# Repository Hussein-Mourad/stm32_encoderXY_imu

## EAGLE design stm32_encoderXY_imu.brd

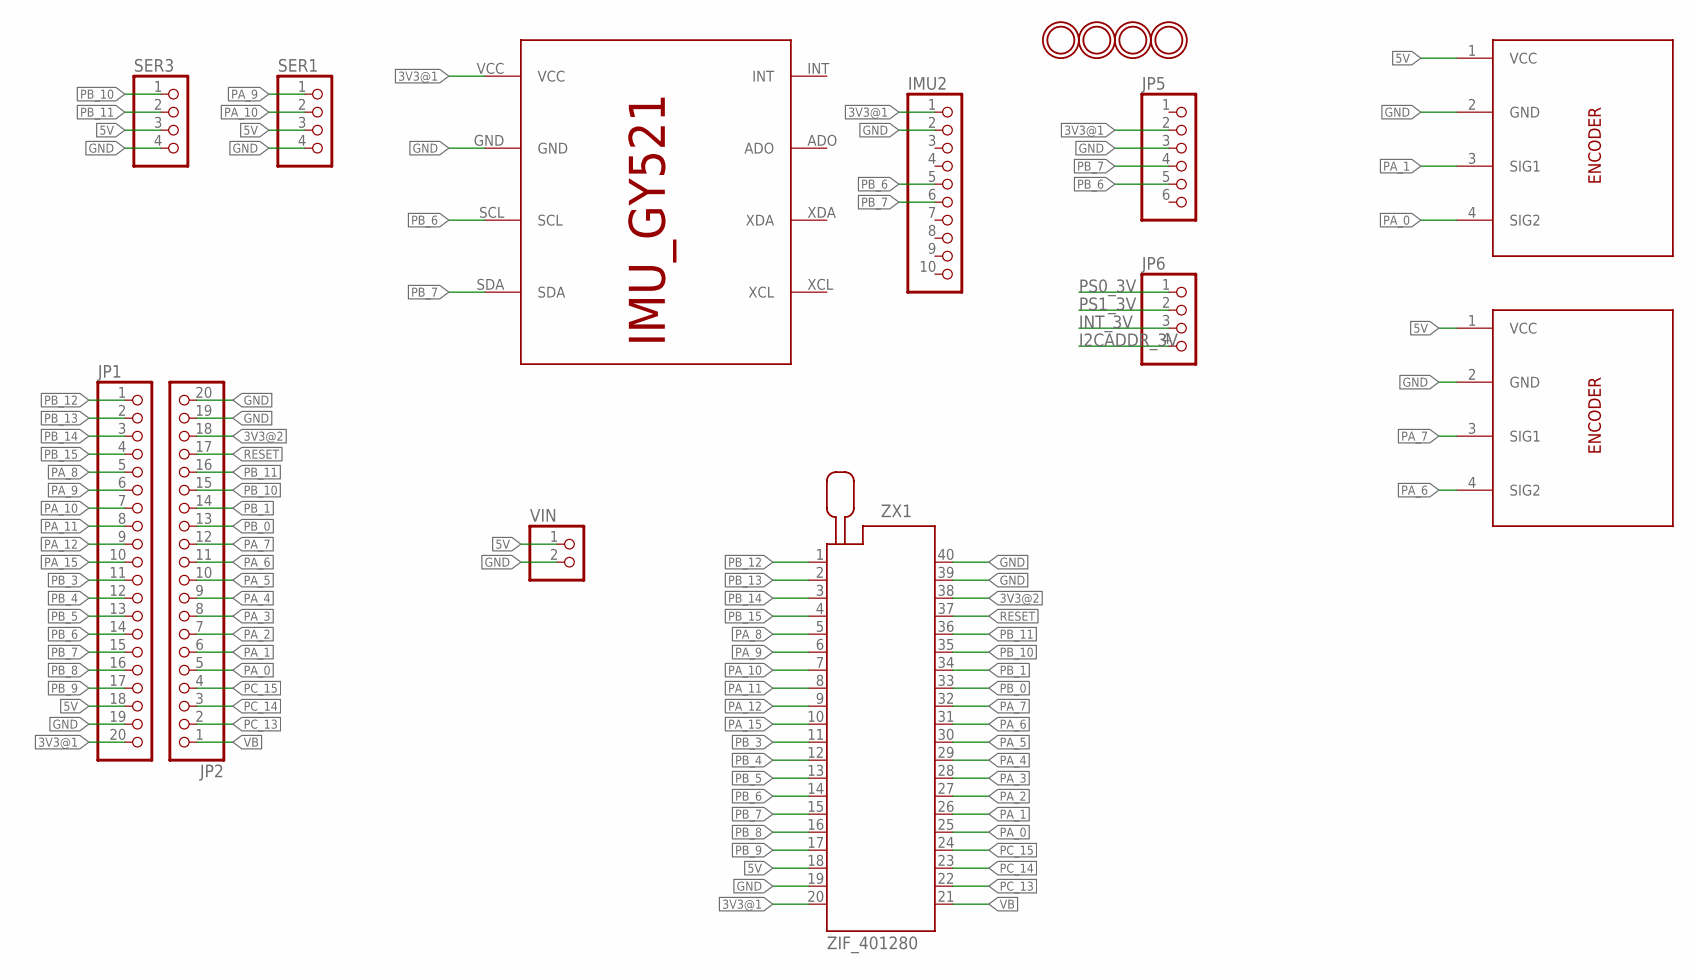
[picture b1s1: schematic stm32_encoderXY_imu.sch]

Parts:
ENC1: ENC_Y; 1X04_DATA
ENC2: ENC_X; 1X04_DATA
IMU1: IMU_ROBOCON_GY521; IMU_GY521
IMU2: PINHD-1X10; 1X10
JP1, JP2: PINHD-1X20; 1X20
JP5: HEADER-1X676MIL; 1X06_ROUND_76
JP6: HEADER-1X476MIL; 1X04_ROUND_76
SER1, SER3: PINHD-4_DATA; 1X04_DATA
U$4, U$5, U$6, U$7: MOUNTINGHOLE2.5_THICK; MOUNTINGHOLE_2.5_PLATED_THICK
VIN: PINHD-2_DATA; 1X02_DATA
ZX1: ZIF_401280; 240-1280-00-0602J

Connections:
3V3@1: IMU1.VCC, IMU2.1, JP1.20, JP5.2, ZX1.20
3V3@2: JP2.18, ZX1.38
5V: ENC1.1 (VCC), ENC2.1 (VCC), JP1.18, SER1.3, SER3.3, VIN.1, ZX1.18
GND: ENC1.2 (GND), ENC2.2 (GND), IMU1.GND, IMU2.2, JP1.19, JP2.19, JP2.20, JP5.3, SER1.4, SER3.4, VIN.2, ZX1.19, ZX1.39, ZX1.40
I2CADDR_3V: JP6.4
INT_3V: JP6.3
PA_0: ENC2.4 (SIG2), JP2.5, ZX1.25
PA_1: ENC2.3 (SIG1), JP2.6, ZX1.26
PA_2: JP2.7, ZX1.27
PA_3: JP2.8, ZX1.28
PA_4: JP2.9, ZX1.29
PA_5: JP2.10, ZX1.30
PA_6: ENC1.4 (SIG2), JP2.11, ZX1.31
PA_7: ENC1.3 (SIG1), JP2.12, ZX1.32
PA_8: JP1.5, ZX1.5
PA_9: JP1.6, SER1.1, ZX1.6
PA_10: JP1.7, SER1.2, ZX1.7
PA_11: JP1.8, ZX1.8
PA_12: JP1.9, ZX1.9
PA_15: JP1.10, ZX1.10
PB_0: JP2.13, ZX1.33
PB_1: JP2.14, ZX1.34
PB_3: JP1.11, ZX1.11
PB_4: JP1.12, ZX1.12
PB_5: JP1.13, ZX1.13
PB_6: IMU1.SCL, IMU2.5, JP1.14, JP5.5, ZX1.14
PB_7: IMU1.SDA, IMU2.6, JP1.15, JP5.4, ZX1.15
PB_8: JP1.16, ZX1.16
PB_9: JP1.17, ZX1.17
PB_10: JP2.15, SER3.1, ZX1.35
PB_11: JP2.16, SER3.2, ZX1.36
PB_12: JP1.1, ZX1.1
PB_13: JP1.2, ZX1.2
PB_14: JP1.3, ZX1.3
PB_15: JP1.4, ZX1.4
PC_13: JP2.2, ZX1.22
PC_14: JP2.3, ZX1.23
PC_15: JP2.4, ZX1.24
PS0_3V: JP6.1
PS1_3V: JP6.2
RESET: JP2.17, ZX1.37
VB: JP2.1, ZX1.21

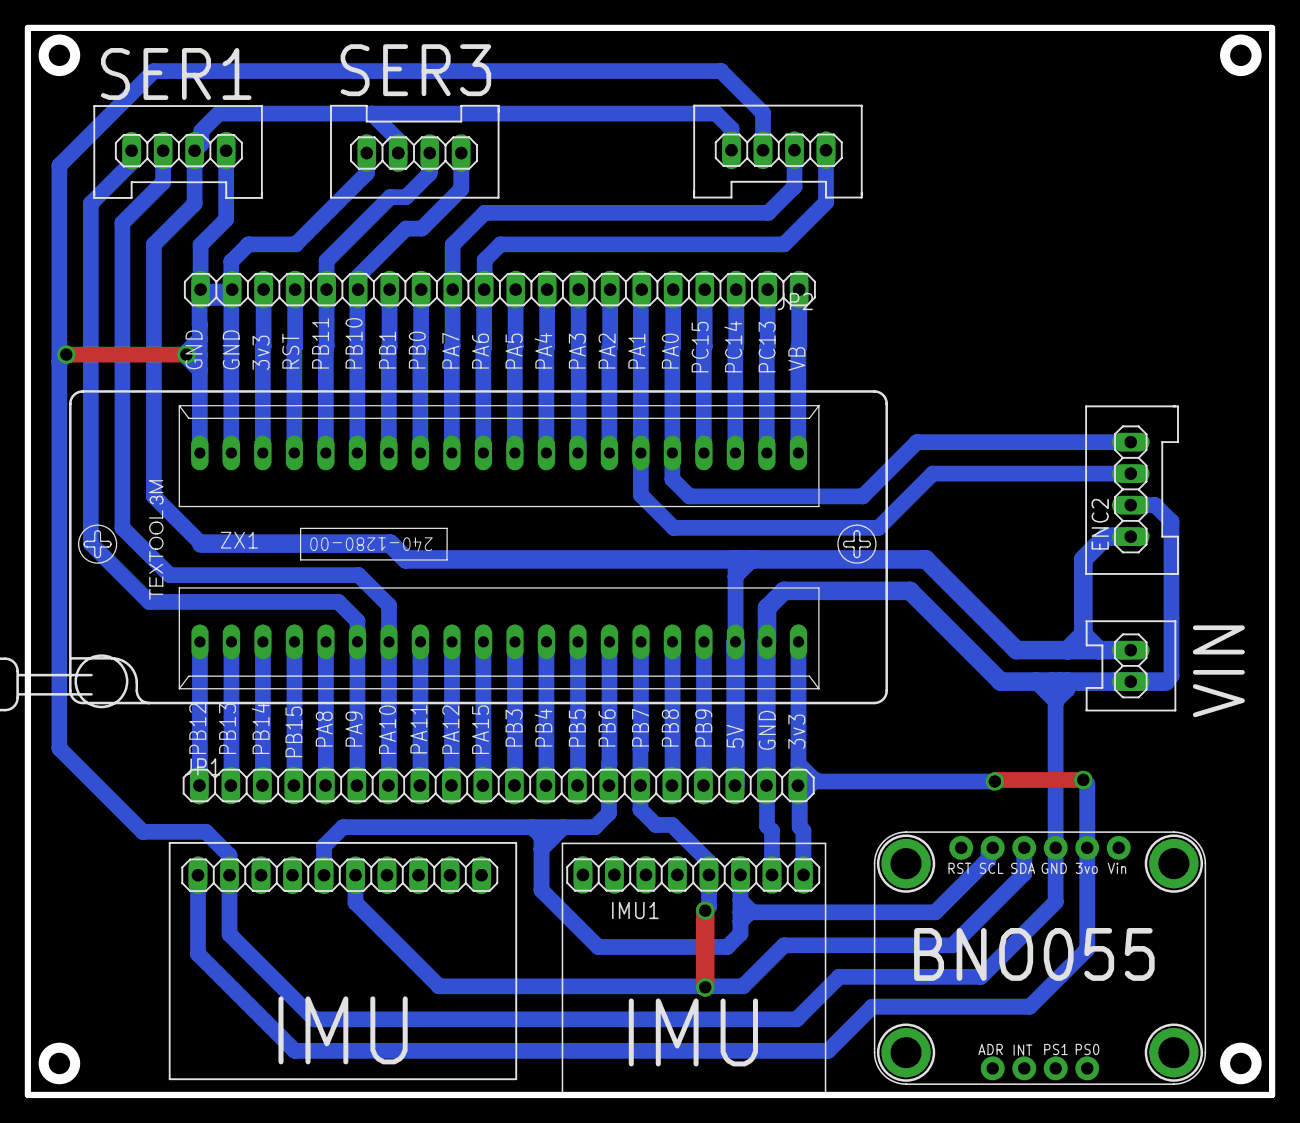
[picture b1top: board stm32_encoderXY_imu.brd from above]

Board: 2 copper layers, 100.3 x 86.0 mm, 16 parts (0 on the bottom side), 38 nets.

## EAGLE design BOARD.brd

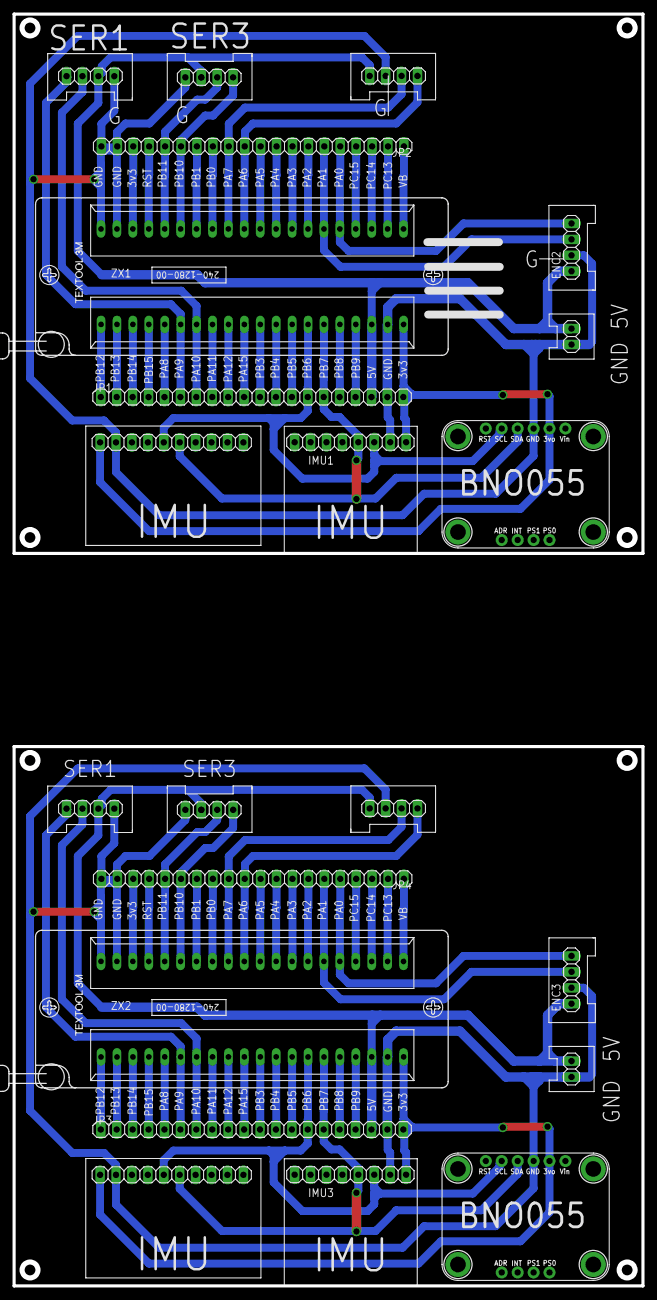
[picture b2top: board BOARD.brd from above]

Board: 2 copper layers, 100.3 x 202.9 mm, 32 parts (0 on the bottom side), 76 nets.

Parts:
ENC1, ENC4: ENC_Y; 1X04_DATA
ENC2, ENC3: ENC_X; 1X04_DATA
IMU1, IMU3: IMU_ROBOCON_GY521; IMU_GY521
IMU2, IMU4: 1X10
JP1, JP2, JP3, JP4: 1X20
JP5, JP7: 1X06_ROUND_76
JP6, JP8: 1X04_ROUND_76
SER1, SER2, SER3, SER4: 1X04_DATA
U$1, U$2, U$3, U$4, U$5, U$6, U$7, U$8: MOUNTINGHOLE2.5_THICK; MOUNTINGHOLE_2.5_PLATED_THICK
VIN, VIN1: 1X02_DATA
ZX1, ZX2: ZIF_401280; 240-1280-00-0602J

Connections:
3V3@1: IMU1.VCC, IMU2.1, JP1.20, JP5.2, ZX1.20
3V3@2: JP2.18, ZX1.38
3V3@3: IMU3.VCC, IMU4.1, JP3.20, JP7.2, ZX2.20
3V3@4: JP4.18, ZX2.38
5V: ENC1.1, ENC2.1, JP1.18, SER1.3, SER3.3, VIN.1, ZX1.18
5V1: ENC3.1, ENC4.1, JP3.18, SER2.3, SER4.3, VIN1.1, ZX2.18
GND: ENC1.2, ENC2.2, IMU1.GND, IMU2.2, JP1.19, JP2.19, JP2.20, JP5.3, SER1.4, SER3.4, VIN.2, ZX1.19, ZX1.39, ZX1.40
GND1: ENC3.2, ENC4.2, IMU3.GND, IMU4.2, JP3.19, JP4.19, JP4.20, JP7.3, SER2.4, SER4.4, VIN1.2, ZX2.19, ZX2.39, ZX2.40
PA_0: ENC2.4, JP2.5, ZX1.25
PA_1: ENC2.3, JP2.6, ZX1.26
PA_2: JP2.7, ZX1.27
PA_3: JP2.8, ZX1.28
PA_4: JP2.9, ZX1.29
PA_5: JP2.10, ZX1.30
PA_6: ENC1.4, JP2.11, ZX1.31
PA_7: ENC1.3, JP2.12, ZX1.32
PA_8: JP1.5, ZX1.5
PA_9: JP1.6, SER1.1, ZX1.6
PA_10: JP1.7, SER1.2, ZX1.7
PA_11: JP1.8, ZX1.8
PA_12: JP1.9, ZX1.9
PA_13: JP3.5, ZX2.5
PA_14: JP3.6, SER4.1, ZX2.6
PA_15: JP1.10, ZX1.10
PA_16: JP3.7, SER4.2, ZX2.7
PA_17: JP3.8, ZX2.8
PA_18: JP3.9, ZX2.9
PA_19: JP3.10, ZX2.10
PA_20: ENC3.4, JP4.5, ZX2.25
PA_21: ENC3.3, JP4.6, ZX2.26
PA_22: JP4.7, ZX2.27
PA_23: JP4.8, ZX2.28
PA_24: JP4.9, ZX2.29
PA_25: JP4.10, ZX2.30
PA_26: ENC4.4, JP4.11, ZX2.31
PA_27: ENC4.3, JP4.12, ZX2.32
PB_0: JP2.13, ZX1.33
PB_1: JP2.14, ZX1.34
PB_2: JP3.1, ZX2.1
PB_3: JP1.11, ZX1.11
PB_4: JP1.12, ZX1.12
PB_5: JP1.13, ZX1.13
PB_6: IMU1.SCL, IMU2.5, JP1.14, JP5.5, ZX1.14
PB_7: IMU1.SDA, IMU2.6, JP1.15, JP5.4, ZX1.15
PB_8: JP1.16, ZX1.16
PB_9: JP1.17, ZX1.17
PB_10: JP2.15, SER3.1, ZX1.35
PB_11: JP2.16, SER3.2, ZX1.36
PB_12: JP1.1, ZX1.1
PB_13: JP1.2, ZX1.2
PB_14: JP1.3, ZX1.3
PB_15: JP1.4, ZX1.4
PB_16: JP3.2, ZX2.2
PB_17: JP3.3, ZX2.3
PB_18: JP3.4, ZX2.4
PB_19: JP3.11, ZX2.11
PB_20: JP3.12, ZX2.12
PB_21: JP3.13, ZX2.13
PB_22: IMU3.SCL, IMU4.5, JP3.14, JP7.5, ZX2.14
PB_23: IMU3.SDA, IMU4.6, JP3.15, JP7.4, ZX2.15
PB_24: JP3.16, ZX2.16
PB_25: JP3.17, ZX2.17
PB_26: JP4.13, ZX2.33
PB_27: JP4.14, ZX2.34
PB_28: JP4.15, SER2.1, ZX2.35
PB_29: JP4.16, SER2.2, ZX2.36
PC_1: JP4.2, ZX2.22
PC_2: JP4.3, ZX2.23
PC_3: JP4.4, ZX2.24
PC_13: JP2.2, ZX1.22
PC_14: JP2.3, ZX1.23
PC_15: JP2.4, ZX1.24
RESET: JP2.17, ZX1.37
RESET1: JP4.17, ZX2.37
VB: JP2.1, ZX1.21
VB1: JP4.1, ZX2.21

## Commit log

2022-02-28 init

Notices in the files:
parts and their libraries:
microbuilder: This work is placed in the public domain, and may be freely used for commercial and non-commercial work with the following conditions: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
